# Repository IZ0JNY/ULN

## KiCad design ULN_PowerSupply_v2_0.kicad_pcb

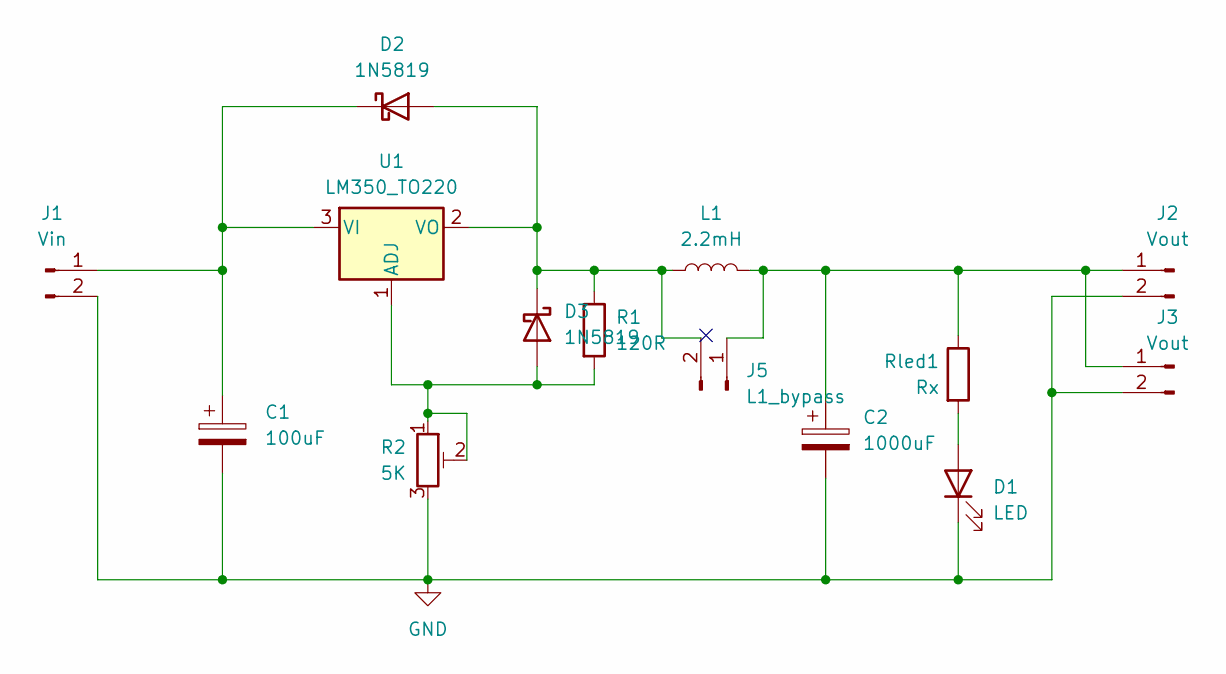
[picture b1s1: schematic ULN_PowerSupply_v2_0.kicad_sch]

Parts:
C1: 100uF; CP_Radial_D8.0mm_P3.50mm
C2: 1000uF; CP_Radial_D16.0mm_P7.50mm
D1: LED; LED_D3.0mm
D2, D3: 1N5819; D_DO-41_SOD81_P10.16mm_Horizontal
J1: Vin; TerminalBlock_bornier-2_P5.08mm
J2, J3: Vout; TerminalBlock_bornier-2_P5.08mm
J5: L1_bypass; TestPoint_2Pads_Pitch2.54mm_Drill0.8mm
L1: 2.2mH; L_Radial_D21.0mm_P19.00mm
R1: 120R; R_Axial_DIN0207_L6.3mm_D2.5mm_P7.62mm_Horizontal
R2: 5K; Potentiometer_Bourns_3296W_Vertical
Rled1: Rx; R_Axial_DIN0207_L6.3mm_D2.5mm_P7.62mm_Horizontal
U1: LM350_TO220; TO-220-3_Vertical

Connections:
GND: C1.2, C2.2, D1.1 (K), J1.2, J2.2, J3.2, R2.3; also elsewhere on the board
unnamed: D1.2 (A), Rled1.2
unnamed: D2.2 (A), D3.1 (K), J5.2, L1.1, R1.1, U1.2 (VO)
unnamed: C1.1, D2.1 (K), J1.1, U1.3 (VI)
unnamed 4: D3.2 (A), R1.2, R2.1, R2.2, U1.1 (ADJ); also elsewhere on the board
unnamed: C2.1, J2.1, J3.1, J5.1, L1.2, Rled1.1

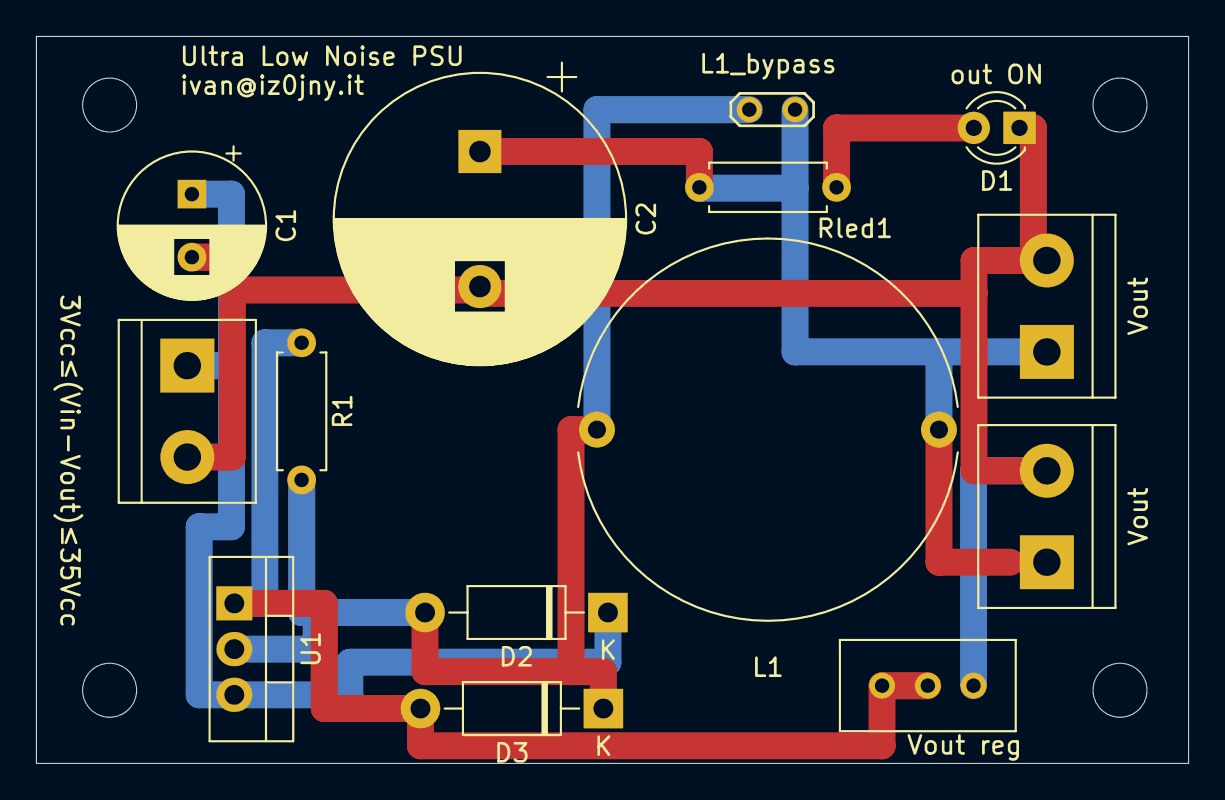
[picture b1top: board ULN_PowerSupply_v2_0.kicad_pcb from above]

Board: 2 copper layers, 64.0 x 40.4 mm, 14 parts (0 on the bottom side), 6 nets.

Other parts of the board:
Vout reg: 5K; Potentiometer_Bourns_3296W_Vertical

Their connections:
GND: Vout reg.3; also elsewhere on the board
unnamed 4: Vout reg.1, Vout reg.2; also elsewhere on the board

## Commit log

2025-03-23 Add files via upload
    version 3.0
